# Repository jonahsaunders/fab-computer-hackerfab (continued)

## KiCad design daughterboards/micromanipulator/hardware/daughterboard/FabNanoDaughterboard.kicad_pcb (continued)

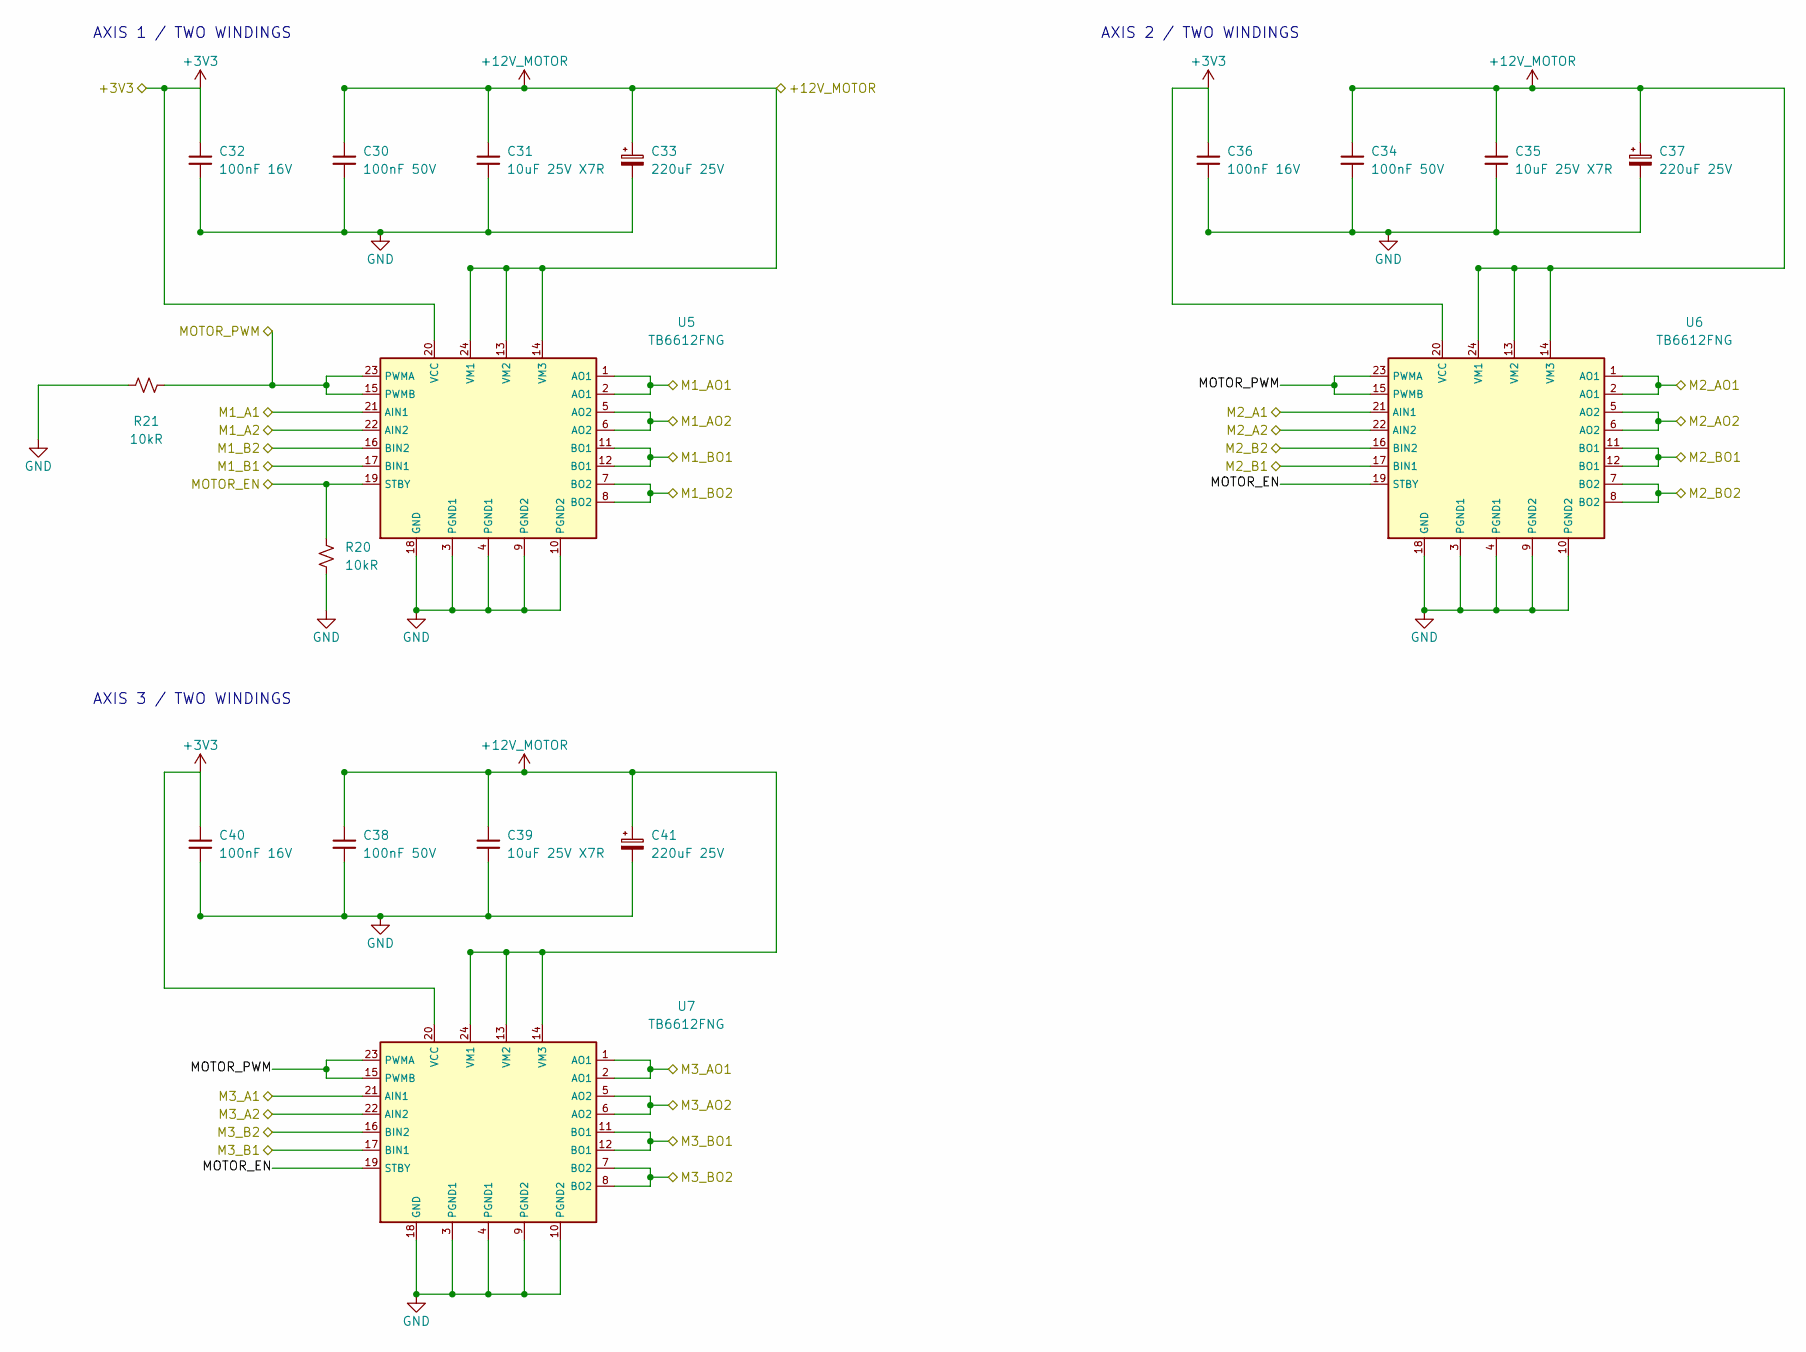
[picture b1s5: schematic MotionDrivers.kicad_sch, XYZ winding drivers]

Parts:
C30, C34, C38: 100nF 50V; C_0603_1608Metric; MPN CC0603KRX7R9BB104; LCSC C14663
C31, C35, C39: 10uF 25V X7R; C_0805_2012Metric; MPN C0805X7R106K250NT; LCSC C2835529
C32, C36, C40: 100nF 16V; C_0402_1005Metric; MPN CL05B104KO5NNNC; LCSC C1525
C33, C37, C41: 220uF 25V; CP_Elec_6.3x7.7; MPN 217EC0037; LCSC C42371908
R20, R21: 10kR; R_0603_1608Metric; MPN 0603WAF1002T5E; LCSC C25804
U5, U6, U7: TB6612FNG; SSOP-24_Toshiba_5.6x7.8mm_P0.65mm; MPN TB6612FNG(O,C,8,EL; LCSC C88224

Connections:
+3V3: C32.1, C36.1, C40.1, U5.20 (VCC), U6.20 (VCC), U7.20 (VCC); also elsewhere on the board
+12V_MOTOR: C30.1, C31.1, C33.1, C34.1, C35.1, C37.1, C38.1, C39.1, C41.1, U5.13 (VM2), U5.14 (VM3), U5.24 (VM1), U6.13 (VM2), U6.14 (VM3), U6.24 (VM1), U7.13 (VM2), U7.14 (VM3), U7.24 (VM1); also elsewhere on the board
/M1_A1: U5.21 (AIN1); also elsewhere on the board
/M1_A2: U5.22 (AIN2); also elsewhere on the board
/M1_AO1: U5.1 (AO1), U5.2 (AO1); also elsewhere on the board
/M1_AO2: U5.5 (AO2), U5.6 (AO2); also elsewhere on the board
/M1_B1: U5.17 (BIN1); also elsewhere on the board
/M1_B2: U5.16 (BIN2); also elsewhere on the board
/M1_BO1: U5.11 (BO1), U5.12 (BO1); also elsewhere on the board
/M1_BO2: U5.7 (BO2), U5.8 (BO2); also elsewhere on the board
/M2_A1: U6.21 (AIN1); also elsewhere on the board
/M2_A2: U6.22 (AIN2); also elsewhere on the board
/M2_AO1: U6.1 (AO1), U6.2 (AO1); also elsewhere on the board
/M2_AO2: U6.5 (AO2), U6.6 (AO2); also elsewhere on the board
/M2_B1: U6.17 (BIN1); also elsewhere on the board
/M2_B2: U6.16 (BIN2); also elsewhere on the board
/M2_BO1: U6.11 (BO1), U6.12 (BO1); also elsewhere on the board
/M2_BO2: U6.7 (BO2), U6.8 (BO2); also elsewhere on the board
/M3_A1: U7.21 (AIN1); also elsewhere on the board
/M3_A2: U7.22 (AIN2); also elsewhere on the board
/M3_AO1: U7.1 (AO1), U7.2 (AO1); also elsewhere on the board
/M3_AO2: U7.5 (AO2), U7.6 (AO2); also elsewhere on the board
/M3_B1: U7.17 (BIN1); also elsewhere on the board
/M3_B2: U7.16 (BIN2); also elsewhere on the board
/M3_BO1: U7.11 (BO1), U7.12 (BO1); also elsewhere on the board
/M3_BO2: U7.7 (BO2), U7.8 (BO2); also elsewhere on the board
/MOTOR_EN: R20.1, U5.19 (STBY), U6.19 (STBY), U7.19 (STBY); also elsewhere on the board
/MOTOR_PWM: R21.1, U5.15 (PWMB), U5.23 (PWMA), U6.15 (PWMB), U6.23 (PWMA), U7.15 (PWMB), U7.23 (PWMA); also elsewhere on the board
GND: C30.2, C31.2, C32.2, C33.2, C34.2, C35.2, C36.2, C37.2, C38.2, C39.2, C40.2, C41.2, R20.2, R21.2, U5.3 (PGND1), U5.4 (PGND1), U5.9 (PGND2), U5.10 (PGND2), U5.18 (GND), U6.3 (PGND1), U6.4 (PGND1), U6.9 (PGND2), U6.10 (PGND2), U6.18 (GND), U7.3 (PGND1), U7.4 (PGND1), U7.9 (PGND2), U7.10 (PGND2), U7.18 (GND); also elsewhere on the board

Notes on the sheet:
AXIS 1 / TWO WINDINGS
AXIS 2 / TWO WINDINGS
AXIS 3 / TWO WINDINGS

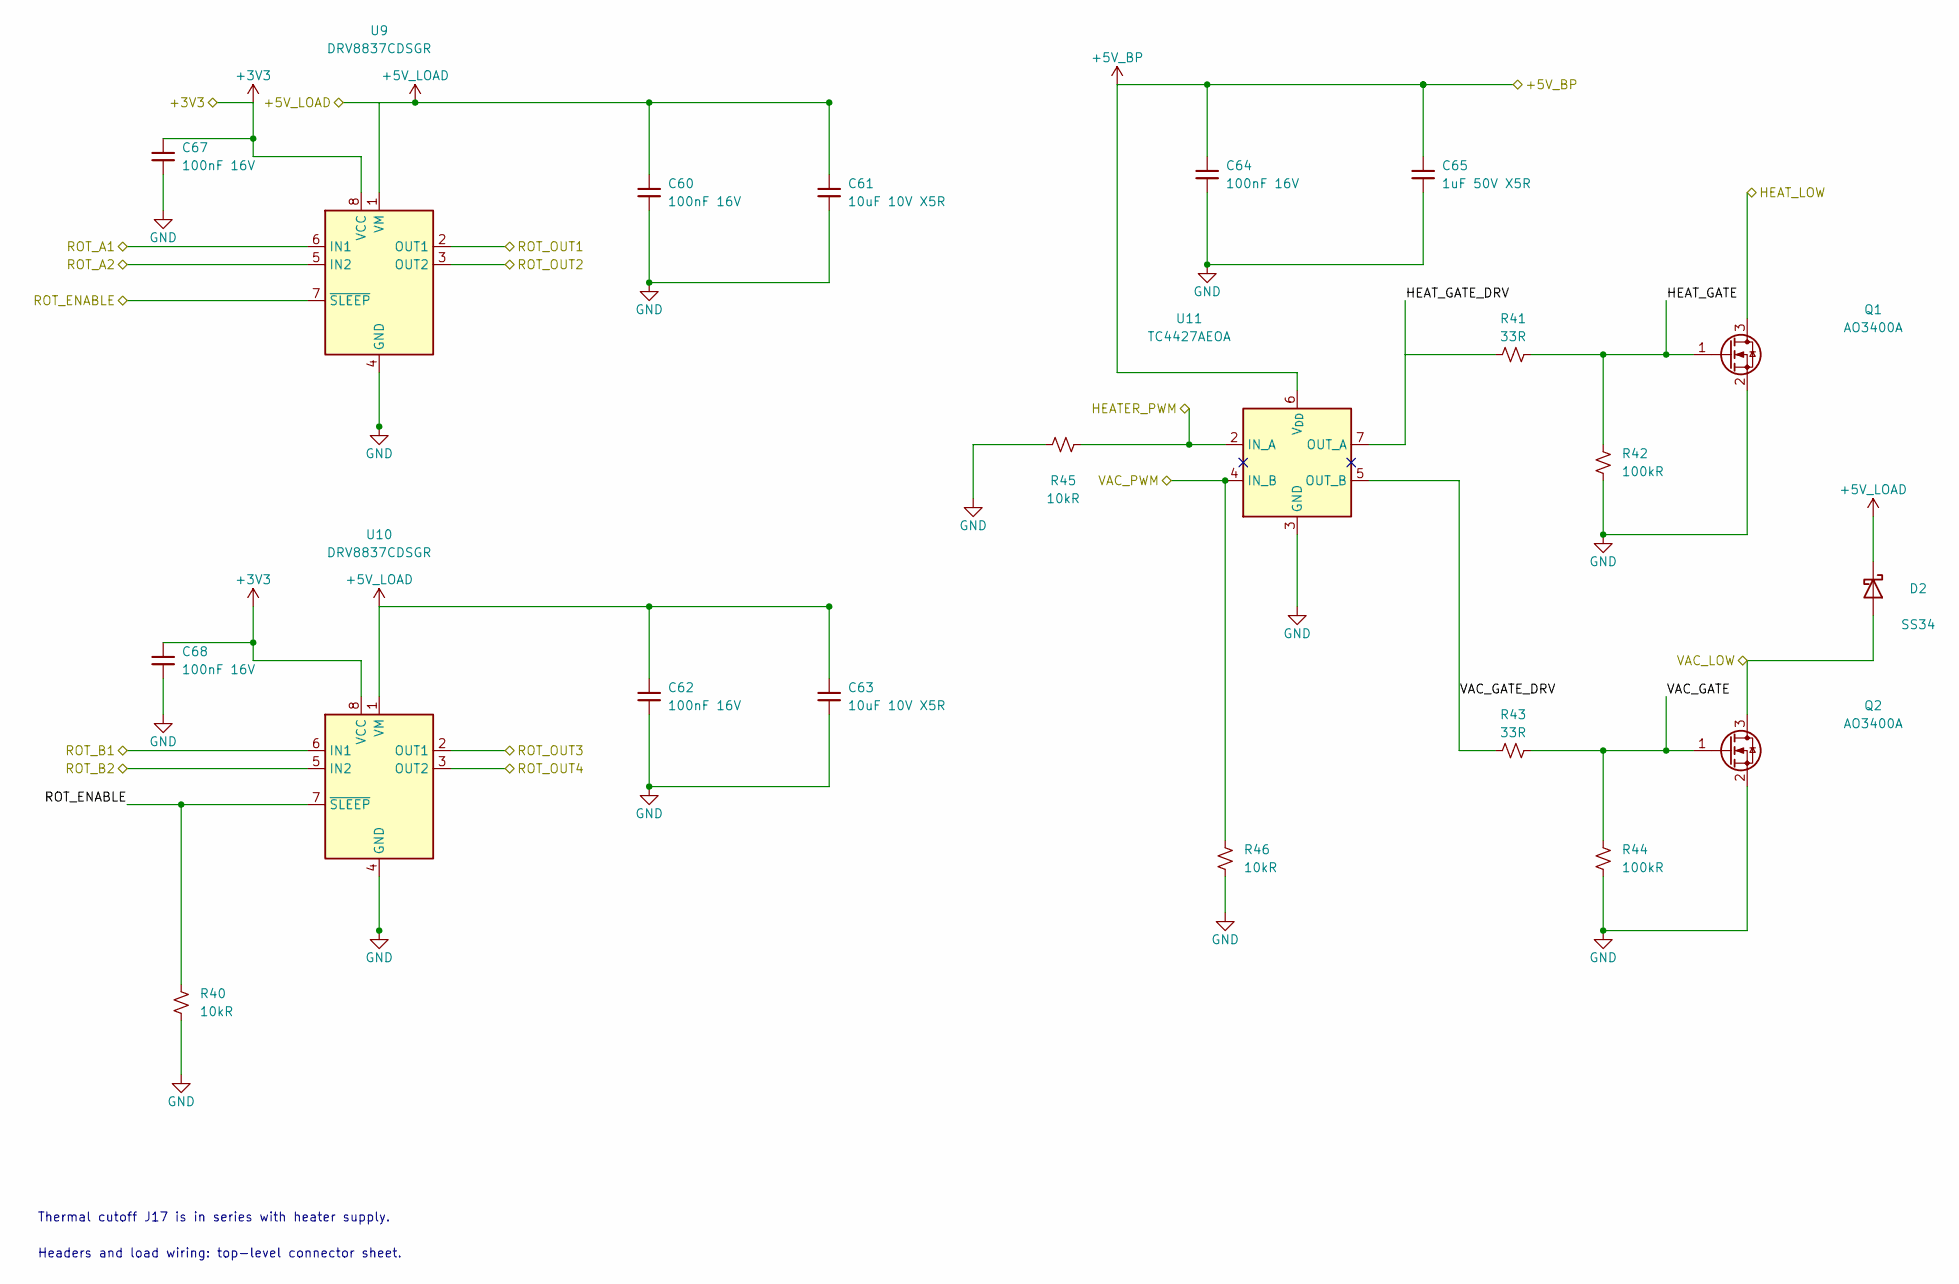
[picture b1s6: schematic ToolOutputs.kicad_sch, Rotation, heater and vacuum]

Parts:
C60, C62, C64, C67, C68: 100nF 16V; C_0402_1005Metric; MPN CL05B104KO5NNNC; LCSC C1525
C61, C63: 10uF 10V X5R; C_0603_1608Metric; MPN CL10A106KP8NNNC; LCSC C19702
C65: 1uF 50V X5R; C_0603_1608Metric; MPN CL10A105KB8NNNC; LCSC C15849
D2: SS34; D_SMA; MPN SS34; LCSC C8678
Q1, Q2: AO3400A; SOT-23; MPN AO3400A; LCSC C20917
R40, R45, R46: 10kR; R_0603_1608Metric; MPN 0603WAF1002T5E; LCSC C25804
R41, R43: 33R; R_0603_1608Metric; MPN 0603WAF330JT5E; LCSC C23140
R42, R44: 100kR; R_0603_1608Metric; MPN 0603WAF1003T5E; LCSC C25803
U9, U10: DRV8837CDSGR; Texas_DSG0008A_WSON-8-1EP_2x2mm_P0.5mm_EP0.9x1.6mm; MPN DRV8837CDSGR; LCSC C191000
U11: TC4427AEOA; SOIC-8_3.9x4.9mm_P1.27mm; MPN TC4427AEOA; LCSC C18690

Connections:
+3V3: C67.1, C68.1, U9.8 (VCC), U10.8 (VCC); also elsewhere on the board
+5V_BP: C64.1, C65.1, U11.6 (V_{DD}); also elsewhere on the board
+5V_LOAD: C60.1, C61.1, C62.1, C63.1, D2.1 (K), U9.1 (VM), U10.1 (VM); also elsewhere on the board
/HEATER_PWM: R45.1, U11.2 (IN_A); also elsewhere on the board
/HEAT_LOW: Q1.3 (D); also elsewhere on the board
/ROT_A1: U9.6 (IN1); also elsewhere on the board
/ROT_A2: U9.5 (IN2); also elsewhere on the board
/ROT_B1: U10.6 (IN1); also elsewhere on the board
/ROT_B2: U10.5 (IN2); also elsewhere on the board
/ROT_ENABLE: R40.1, U9.7 (~SLEEP), U10.7 (~SLEEP); also elsewhere on the board
/ROT_OUT1: U9.2 (OUT1); also elsewhere on the board
/ROT_OUT2: U9.3 (OUT2); also elsewhere on the board
/ROT_OUT3: U10.2 (OUT1); also elsewhere on the board
/ROT_OUT4: U10.3 (OUT2); also elsewhere on the board
/ToolOutputs/HEAT_GATE: Q1.1 (G), R41.2, R42.1
/ToolOutputs/HEAT_GATE_DRV: R41.1, U11.7 (OUT_A)
/ToolOutputs/VAC_GATE: Q2.1 (G), R43.2, R44.1
/ToolOutputs/VAC_GATE_DRV: R43.1, U11.5 (OUT_B)
/VAC_LOW: D2.2 (A), Q2.3 (D); also elsewhere on the board
/VAC_PWM: R46.1, U11.4 (IN_B); also elsewhere on the board
GND: C60.2, C61.2, C62.2, C63.2, C64.2, C65.2, C67.2, C68.2, Q1.2 (S), Q2.2 (S), R40.2, R42.2, R44.2, R45.2, R46.2, U9.4 (GND), U9.9 (GND), U10.4 (GND), U10.9 (GND), U11.3 (GND); also elsewhere on the board

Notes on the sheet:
Thermal cutoff J17 is in series with heater supply.
Headers and load wiring: top-level connector sheet.

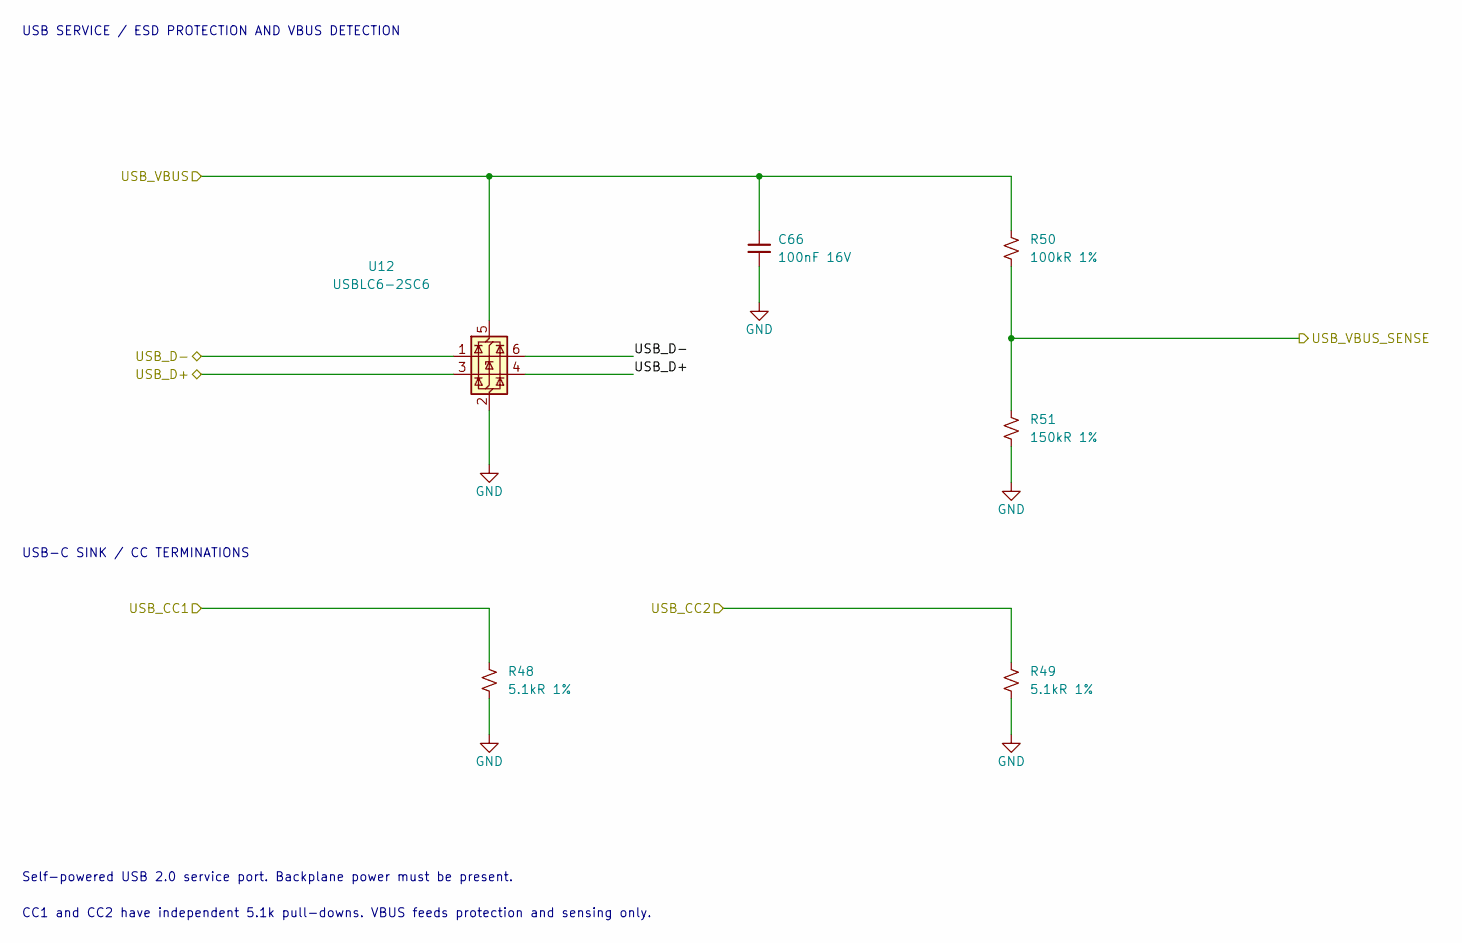
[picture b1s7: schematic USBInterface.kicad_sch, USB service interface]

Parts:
C66: 100nF 16V; C_0402_1005Metric; MPN CL05B104KO5NNNC; LCSC C1525
R48, R49: 5.1kR 1%; R_0603_1608Metric; MPN 0603WAF5101T5E; LCSC C23186
R50: 100kR 1%; R_0603_1608Metric; MPN 0603WAF1003T5E; LCSC C25803
R51: 150kR 1%; R_0603_1608Metric; MPN 0603WAF1503T5E; LCSC C22807
U12: USBLC6-2SC6; SOT-23-6; MPN USBLC6-2SC6; LCSC C7519

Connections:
/USB_CC1: R48.1; also elsewhere on the board
/USB_CC2: R49.1; also elsewhere on the board
/USB_D+: U12.3 (I/O2), U12.4 (I/O2); also elsewhere on the board
/USB_D-: U12.1 (I/O1), U12.6 (I/O1); also elsewhere on the board
/USB_VBUS: C66.1, R50.1, U12.5 (VBUS); also elsewhere on the board
/USB_VBUS_SENSE: R50.2, R51.1; also elsewhere on the board
GND: C66.2, R48.2, R49.2, R51.2, U12.2 (GND); also elsewhere on the board

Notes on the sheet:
USB SERVICE / ESD PROTECTION AND VBUS DETECTION
USB-C SINK / CC TERMINATIONS
Self-powered USB 2.0 service port. Backplane power must be present.
CC1 and CC2 have independent 5.1k pull-downs. VBUS feeds protection and sensing only.

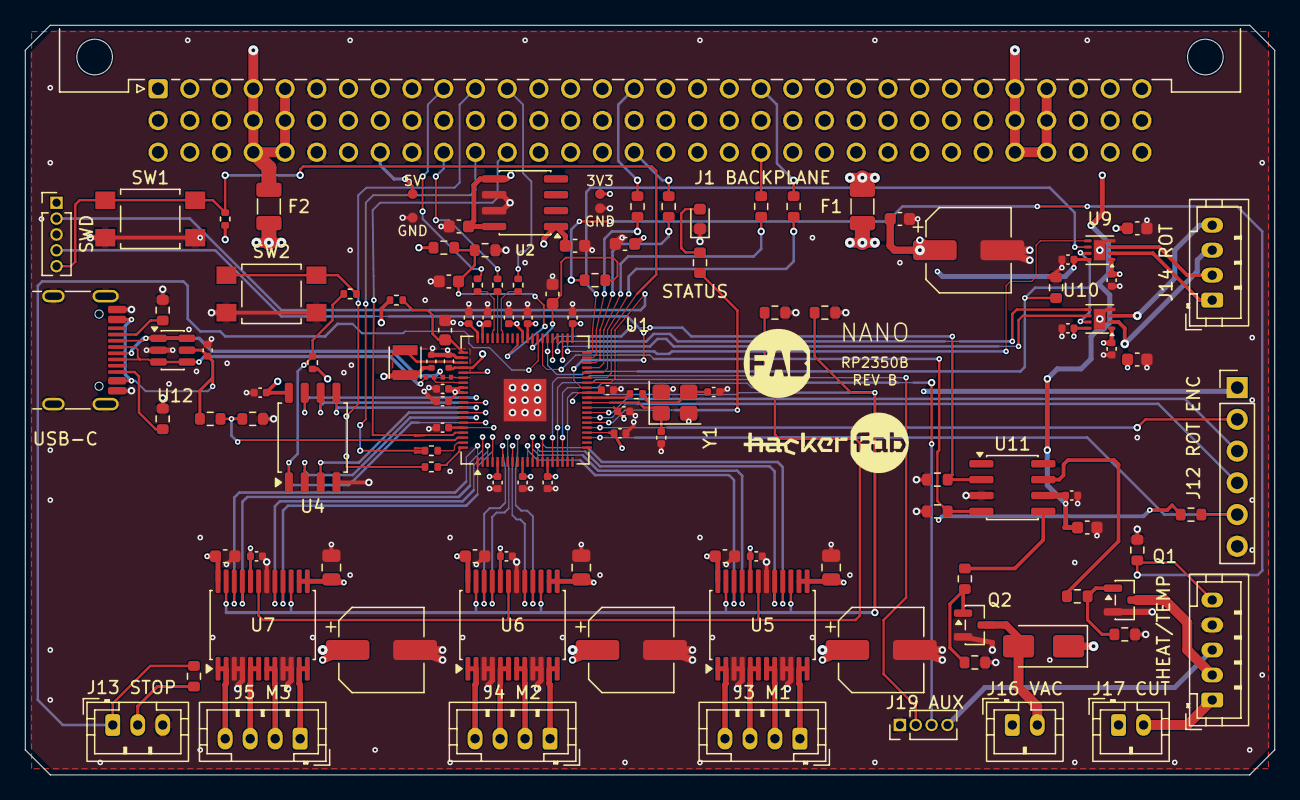
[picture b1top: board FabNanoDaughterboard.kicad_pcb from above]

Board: 4 copper layers, 100.0 x 60.0 mm, 121 parts (0 on the bottom side), 105 nets.

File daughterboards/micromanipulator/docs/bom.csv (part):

Reference,Value,Footprint,Manufacturer part number,Manufacturer,LCSC,Quantity,Procurement status
J1,DIN96 / male right-angle,FabNano:DIN96_Male_Horizontal,9001-11961C00A,WingTAT,C5173361,1,Manufacturer hole pattern and JLCPCB assembly catalog checked 2026-11-07; confirm order inventory
J2,SWD / RP2350,Connector_PinHeader_1.27mm:PinHeader_1x05_P1.27mm_Vertical,PH1.27-01-05PZD,XUNPU,C41360740,1,Manufacturer hole pattern and JLCPCB assembly catalog checked 2026-11-07; confirm order inventory
J3,MOTOR 1,Connector_JST:JST_PH_B4B-PH-K_1x04_P2.00mm_Vertical,B4B-PH-K-S(LF)(SN),JST,C131334,1,Manufacturer hole pattern and JLCPCB assembly catalog checked 2026-11-07; confirm order inventory
J4,MOTOR 2,Connector_JST:JST_PH_B4B-PH-K_1x04_P2.00mm_Vertical,B4B-PH-K-S(LF)(SN),JST,C131334,1,Manufacturer hole pattern and JLCPCB assembly catalog checked 2026-11-07; confirm order inventory
J5,MOTOR 3,Connector_JST:JST_PH_B4B-PH-K_1x04_P2.00mm_Vertical,B4B-PH-K-S(LF)(SN),JST,C131334,1,Manufacturer hole pattern and JLCPCB assembly catalog checked 2026-11-07; confirm order inventory
J12,ROTATION ENCODER,Connector_PinHeader_2.54mm:PinHeader_1x06_P2.54mm_Vertical,2.54-1x6PStraight pin,BOOMELE,C37208,1,Manufacturer hole pattern and JLCPCB assembly catalog checked 2026-11-07; confirm order inventory
J13,ENDSTOP,Connector_JST:JST_PH_B3B-PH-K_1x03_P2.00mm_Vertical,B3B-PH-K-S(LF)(SN),JST,C131339,1,Manufacturer hole pattern and JLCPCB assembly catalog checked 2026-11-07; confirm order inventory
J14,ROTATION MOTOR,Connector_JST:JST_PH_B4B-PH-K_1x04_P2.00mm_Vertical,B4B-PH-K-S(LF)(SN),JST,C131334,1,Manufacturer hole pattern and JLCPCB assembly catalog checked 2026-11-07; confirm order inventory
J15,HEATER + TEMP,Connector_JST:JST_PH_B5B-PH-K_1x05_P2.00mm_Vertical,B5B-PH-K-S(LF)(SN),JST,C157993,1,Manufacturer hole pattern and JLCPCB assembly catalog checked 2026-11-07; confirm order inventory
J16,VACUUM / 5 V,Connector_JST:JST_PH_B2B-PH-K_1x02_P2.00mm_Vertical,B2B-PH-K-S(LF)(SN),JST,C131337,1,Manufacturer hole pattern and JLCPCB assembly catalog checked 2026-11-07; confirm order inventory
J17,THERMAL CUTOFF,Connector_JST:JST_PH_B2B-PH-K_1x02_P2.00mm_Vertical,B2B-PH-K-S(LF)(SN),JST,C131337,1,Manufacturer hole pattern and JLCPCB assembly catalog checked 2026-11-07; confirm order inventory
J18,USB-C / SERVICE,Connector_USB:USB_C_Receptacle_HRO_TYPE-C-31-M-12,TYPE-C-31-M-12,HRO,C165948,1,"Exact part, package/model and JLCPCB catalog checked 2026-11-07; confirm inventory"
J19,TOOL PWM,Connector_PinHeader_1.27mm:PinHeader_1x04_P1.27mm_Vertical,PH1.27-01-04PZD,XUNPU,C41360739,1,Manufacturer hole pattern and JLCPCB assembly catalog checked 2026-11-07; confirm order inventory
C10,4.7uF 16V X5R,Capacitor_SMD:C_0603_1608Metric,CL10A475KO8NNNC,Samsung Electro-Mechanics,C19666,1,Samsung bias data and JLCPCB catalog/package checked 2026-11-07; confirm order inventory
C11,4.7uF 6.3V X5R,FabNano:C_0402_RP2350_Regulator,GRM155R60J475ME47D,Murata,C82453,1,Exact existing part and JLCPCB code checked 2026-11-07; confirm inventory
C12,4.7uF 6.3V X5R,FabNano:C_0402_RP2350_Regulator,GRM155R60J475ME47D,Murata,C82453,1,Exact existing part and JLCPCB code checked 2026-11-07; confirm inventory
C13,100nF 25V,Capacitor_SMD:C_0402_1005Metric,CL05B104KA5NNNC,Samsung Electro-Mechanics,C155422,1,Manufacturer dimensions/ratings and JLCPCB catalog checked 2026-11-07; confirm order inventory
C14,15pF C0G,Capacitor_SMD:C_0402_1005Metric,0402CG150J500NT,Guangdong Fenghua Advanced Technology,C1548,1,Manufacturer dimensions/ratings and JLCPCB catalog checked 2026-11-07; confirm order inventory
C15,15pF C0G,Capacitor_SMD:C_0402_1005Metric,0402CG150J500NT,Guangdong Fenghua Advanced Technology,C1548,1,Manufacturer dimensions/ratings and JLCPCB catalog checked 2026-11-07; confirm order inventory
C16,100nF 25V,Capacitor_SMD:C_0402_1005Metric,CL05B104KA5NNNC,Samsung Electro-Mechanics,C155422,1,Manufacturer dimensions/ratings and JLCPCB catalog checked 2026-11-07; confirm order inventory
C17,100nF 25V,Capacitor_SMD:C_0402_1005Metric,CL05B104KA5NNNC,Samsung Electro-Mechanics,C155422,1,Manufacturer dimensions/ratings and JLCPCB catalog checked 2026-11-07; confirm order inventory
C18,100nF 25V,Capacitor_SMD:C_0402_1005Metric,CL05B104KA5NNNC,Samsung Electro-Mechanics,C155422,1,Manufacturer dimensions/ratings and JLCPCB catalog checked 2026-11-07; confirm order inventory
C19,100nF 25V,Capacitor_SMD:C_0402_1005Metric,CL05B104KA5NNNC,Samsung Electro-Mechanics,C155422,1,Manufacturer dimensions/ratings and JLCPCB catalog checked 2026-11-07; confirm order inventory
C20,100nF 25V,Capacitor_SMD:C_0402_1005Metric,CL05B104KA5NNNC,Samsung Electro-Mechanics,C155422,1,Manufacturer dimensions/ratings and JLCPCB catalog checked 2026-11-07; confirm order inventory
C21,100nF 25V,Capacitor_SMD:C_0402_1005Metric,CL05B104KA5NNNC,Samsung Electro-Mechanics,C155422,1,Manufacturer dimensions/ratings and JLCPCB catalog checked 2026-11-07; confirm order inventory
C22,100nF 25V,Capacitor_SMD:C_0402_1005Metric,CL05B104KA5NNNC,Samsung Electro-Mechanics,C155422,1,Manufacturer dimensions/ratings and JLCPCB catalog checked 2026-11-07; confirm order inventory
C23,100nF 25V,Capacitor_SMD:C_0402_1005Metric,CL05B104KA5NNNC,Samsung Electro-Mechanics,C155422,1,Manufacturer dimensions/ratings and JLCPCB catalog checked 2026-11-07; confirm order inventory
C24,100nF 25V,Capacitor_SMD:C_0402_1005Metric,CL05B104KA5NNNC,Samsung Electro-Mechanics,C155422,1,Manufacturer dimensions/ratings and JLCPCB catalog checked 2026-11-07; confirm order inventory
C25,100nF 25V,Capacitor_SMD:C_0402_1005Metric,CL05B104KA5NNNC,Samsung Electro-Mechanics,C155422,1,Manufacturer dimensions/ratings and JLCPCB catalog checked 2026-11-07; confirm order inventory
C26,100nF 25V,Capacitor_SMD:C_0402_1005Metric,CL05B104KA5NNNC,Samsung Electro-Mechanics,C155422,1,Manufacturer dimensions/ratings and JLCPCB catalog checked 2026-11-07; confirm order inventory
C27,100nF 25V,Capacitor_SMD:C_0402_1005Metric,CL05B104KA5NNNC,Samsung Electro-Mechanics,C155422,1,Manufacturer dimensions/ratings and JLCPCB catalog checked 2026-11-07; confirm order inventory
C53,100nF 25V,Capacitor_SMD:C_0402_1005Metric,CL05B104KA5NNNC,Samsung Electro-Mechanics,C155422,1,Manufacturer dimensions/ratings and JLCPCB catalog checked 2026-11-07; confirm order inventory
C54,100nF 25V,Capacitor_SMD:C_0402_1005Metric,CL05B104KA5NNNC,Samsung Electro-Mechanics,C155422,1,Manufacturer dimensions/ratings and JLCPCB catalog checked 2026-11-07; confirm order inventory
L2,3.3uH,Hack_Passives:L_Murata_DFE252012F_2.5x2.0mm,DFE252012F-3R3M=P2,Murata,C2041573,1,Manufacturer dimensions/ratings and JLCPCB catalog checked 2026-11-07; confirm order inventory
R7,27R,FabNano:R_0201_Yageo_Reflow,RC0201FR-0727RL,YAGEO,C273268,1,JLCPCB Standard assembly catalog and manufacturer land pattern checked 2026-11-07; confirm order inventory
R8,27R,FabNano:R_0201_Yageo_Reflow,RC0201FR-0727RL,YAGEO,C273268,1,JLCPCB Standard assembly catalog and manufacturer land pattern checked 2026-11-07; confirm order inventory
R10,33R,Resistor_SMD:R_0402_1005Metric,0402WGF330JTCE,Uniroyal Electronics,C25105,1,Manufacturer dimensions/ratings and JLCPCB catalog checked 2026-11-07; confirm order inventory
R11,10kR,Resistor_SMD:R_0402_1005Metric,0402WGF1002TCE,Uniroyal Electronics,C25744,1,Manufacturer dimensions/ratings and JLCPCB catalog checked 2026-11-07; confirm order inventory
R12,1kR,Resistor_SMD:R_0402_1005Metric,0402WGF1001TCE,Uniroyal Electronics,C11702,1,Manufacturer dimensions/ratings and JLCPCB catalog checked 2026-11-07; confirm order inventory
R13,10kR,Resistor_SMD:R_0402_1005Metric,0402WGF1002TCE,Uniroyal Electronics,C25744,1,Manufacturer dimensions/ratings and JLCPCB catalog checked 2026-11-07; confirm order inventory
R14,1kR,Resistor_SMD:R_0402_1005Metric,0402WGF1001TCE,Uniroyal Electronics,C11702,1,Manufacturer dimensions/ratings and JLCPCB catalog checked 2026-11-07; confirm order inventory
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
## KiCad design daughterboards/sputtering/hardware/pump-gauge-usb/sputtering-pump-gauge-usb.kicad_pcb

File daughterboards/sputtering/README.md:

# Sputtering cards

Two cards for the sputtering backplane. No MCU on either; the backplane's RP2350B drives them.

[Repository overview](../../README.md#sputtering-cards) · [Review and validation](docs/validation.md) · [Manufacturing guide](../../docs/manufacturing/README.md#sputtering-cards)

| Board | Slot | Size | Open in KiCad 10 | Review |
| --- | --- | --- | --- | --- |
| Pump + gauge + USB | J1 | 100 × 65 mm, 2 layers | [Project](hardware/pump-gauge-usb/sputtering-pump-gauge-usb.kicad_pro) | [Schematic](docs/sputtering-pump-gauge-usb-schematic.pdf), [3D](docs/sputtering-pump-gauge-usb-3d.png), [BOM](../../docs/manufacturing/sputtering-pump-gauge-usb/BOM.csv) |
| Alicat | J2 | 100 × 85 mm, 2 layers | [Project](hardware/alicat/sputtering-alicat.kicad_pro) | [Schematic](docs/sputtering-alicat-schematic.pdf), [3D](docs/sputtering-alicat-3d.png), [BOM](../../docs/manufacturing/sputtering-alicat/BOM.csv) |

Keep this folder together: libraries resolve from [`hardware/libraries/`](hardware/libraries/).

The projects also use the standard symbol and footprint libraries installed with KiCad 10. Design sources, local libraries, schematic PDFs, renders and review notes live in this section. Fabrication exports follow the repository's shared manufacturing layout:

| Board | Fabrication | Assembly |
| --- | --- | --- |
| Pump + gauge + USB | [Gerbers and drills](../../docs/manufacturing/sputtering-pump-gauge-usb/Gerbers.zip) | [BOM](../../docs/manufacturing/sputtering-pump-gauge-usb/BOM.csv) · [CPL](../../docs/manufacturing/sputtering-pump-gauge-usb/CPL.csv) |
| Alicat | [Gerbers and drills](../../docs/manufacturing/sputtering-alicat/Gerbers.zip) | [BOM](../../docs/manufacturing/sputtering-alicat/BOM.csv) · [CPL](../../docs/manufacturing/sputtering-alicat/CPL.csv) |

## Backplane connections

Slot names below refer to the host: use **J1 for pump + gauge + USB** and **J2 for Alicat**. Both cards name their own DIN96 plug J1. These slot assignments use the host's slot-specific UART and AUX connections; the cards are not interchangeable between slots.

| Card | Backplane use |
| --- | --- |
| Pump + gauge + USB | UART0 pump (RS-485), GPIO40 direction; I²C0 gauge ADC (0x48); GPIO22/23 PIO-USB host |
| Alicat | UART1 argon, GPIO24/25 PIO UART oxygen (RS-232) |

## Review status

The [PR #16 connector update](https://github.com/jonahsaunders/fab-computer-hackerfab/pull/16), submitted by [jacobro100](https://github.com/jacobro100), adds pump-card screw terminals and male Alicat DB9 connectors. KiCad 10.0.6 reported no ERC errors or warnings and no DRC errors, unconnected items or schematic-parity findings. DRC reported **9 warnings on pump + gauge + USB** and **24 warnings on Alicat**. See the [review record](docs/validation.md) for categories, reproduction commands and remaining manufacturing and bench checks.

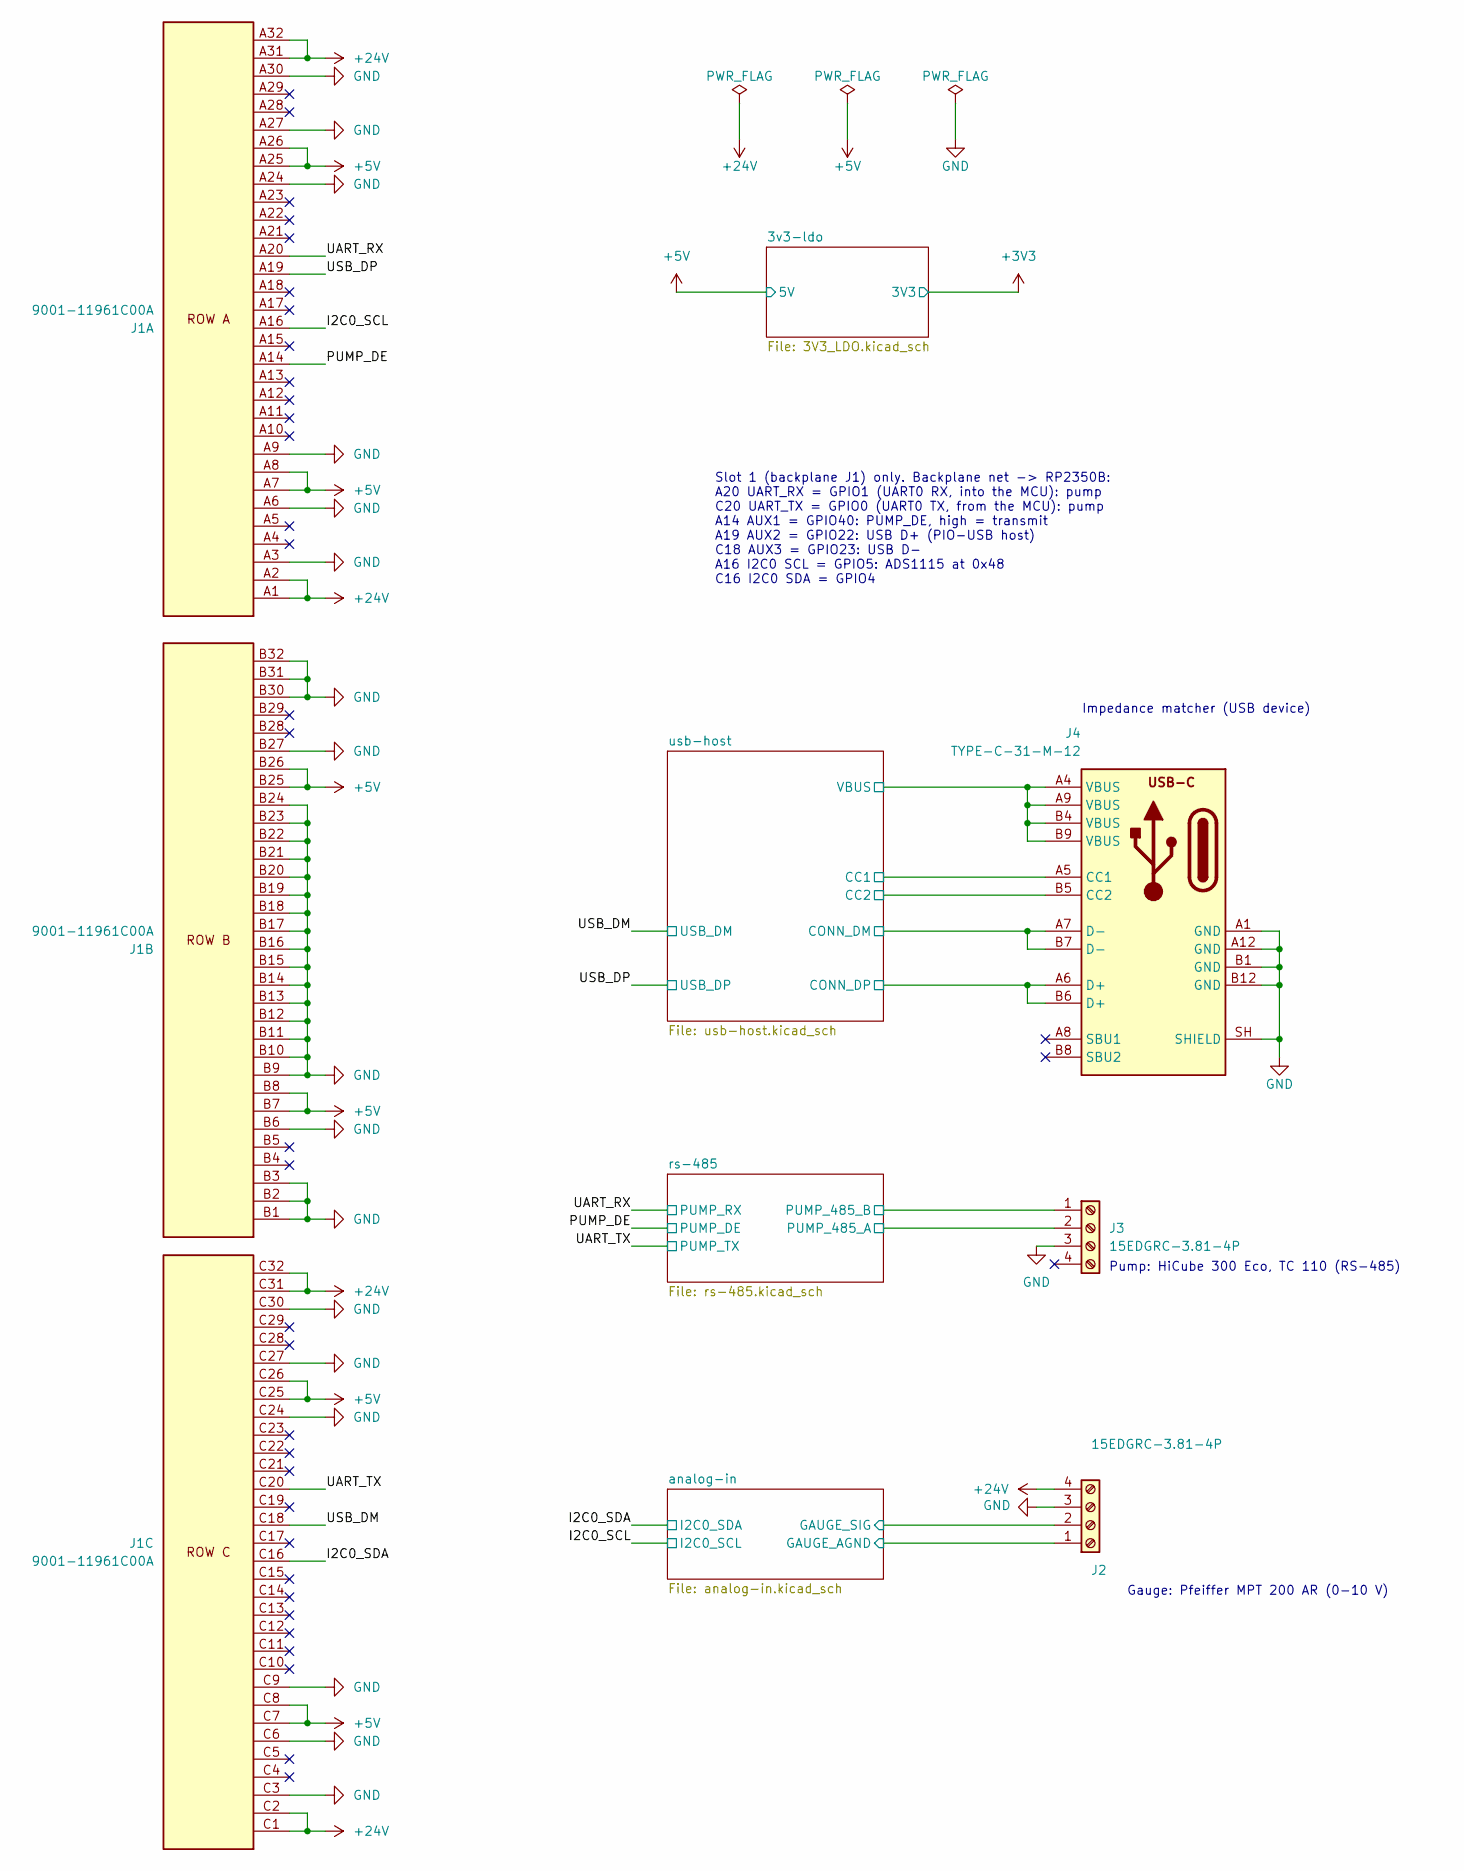
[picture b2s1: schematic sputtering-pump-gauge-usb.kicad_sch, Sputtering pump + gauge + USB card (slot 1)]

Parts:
J1: 9001-11961C00A; WingTAT_9001-11961C00A_DIN41612_C_3x32_RightAngle; LCSC C5173361
J2, J3: 15EDGRC-3.81-4P; Kangnex_WJ15EDGRC-3.81_1x04_P3.81mm_Horizontal; MPN Kangnex WJ15EDGRC-3.81-04P-14-00A; LCSC C7245
J4: TYPE-C-31-M-12; USB_C_Receptacle_HRO_TYPE-C-31-M-12; MPN TYPE-C-31-M-12; LCSC C165948

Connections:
+5V: J1.A7, J1.A8, J1.A25, J1.A26, J1.B7, J1.B8, J1.B25, J1.B26, J1.C7, J1.C8, J1.C25, J1.C26; also elsewhere on the board
+24V: J1.A1, J1.A2, J1.A31, J1.A32, J1.C1, J1.C2, J1.C31, J1.C32, J2.4
/I2C0_SCL: J1.A16; also elsewhere on the board
/I2C0_SDA: J1.C16; also elsewhere on the board
/PUMP_DE: J1.A14; also elsewhere on the board
/UART_RX: J1.A20; also elsewhere on the board
/UART_TX: J1.C20; also elsewhere on the board
/USB_DM: J1.C18; also elsewhere on the board
/USB_DP: J1.A19; also elsewhere on the board
/analog-in/GAUGE_AGND: J2.1; also elsewhere on the board
/analog-in/GAUGE_SIG: J2.2; also elsewhere on the board
/rs-485/PUMP_485_A: J3.2; also elsewhere on the board
/rs-485/PUMP_485_B: J3.1; also elsewhere on the board
/usb-host/CC1: J4.A5 (CC1); also elsewhere on the board
/usb-host/CC2: J4.B5 (CC2); also elsewhere on the board
/usb-host/CONN_DM: J4.A7 (D-), J4.B7 (D-); also elsewhere on the board
/usb-host/CONN_DP: J4.A6 (D+), J4.B6 (D+); also elsewhere on the board
/usb-host/VBUS: J4.A4 (VBUS), J4.A9 (VBUS), J4.B4 (VBUS), J4.B9 (VBUS); also elsewhere on the board
GND: J1.A3, J1.A6, J1.A9, J1.A24, J1.A27, J1.A30, J1.B1, J1.B2, J1.B3, J1.B6, J1.B9, J1.B10, J1.B11, J1.B12, J1.B13, J1.B14, J1.B15, J1.B16, J1.B17, J1.B18, J1.B19, J1.B20, J1.B21, J1.B22, J1.B23, J1.B24, J1.B27, J1.B30, J1.B31, J1.B32, J1.C3, J1.C6, J1.C9, J1.C24, J1.C27, J1.C30, J2.3, J3.3, J4.A1 (GND), J4.A12 (GND), J4.B1 (GND), J4.B12 (GND), J4.SH (SHIELD); also elsewhere on the board

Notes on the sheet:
Pump: HiCube 300 Eco, TC 110 (RS-485)
Impedance matcher (USB device)
Gauge: Pfeiffer MPT 200 AR (0-10 V)
Slot 1 (backplane J1) only. Backplane net -> RP2350B: A20 UART_RX = GPIO1 (UART0 RX, into the MCU): pump C20 UART_TX = GPIO0 (UART0 TX, from the MCU): pump A14 AUX1 = GPIO40: PUMP_DE, high = transmit A19 AUX2 = GPIO22: USB D+ (PIO-USB host) C18 AUX3 = GPIO23: USB D- A16 I2C0 SCL = GPIO5: ADS1115 at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

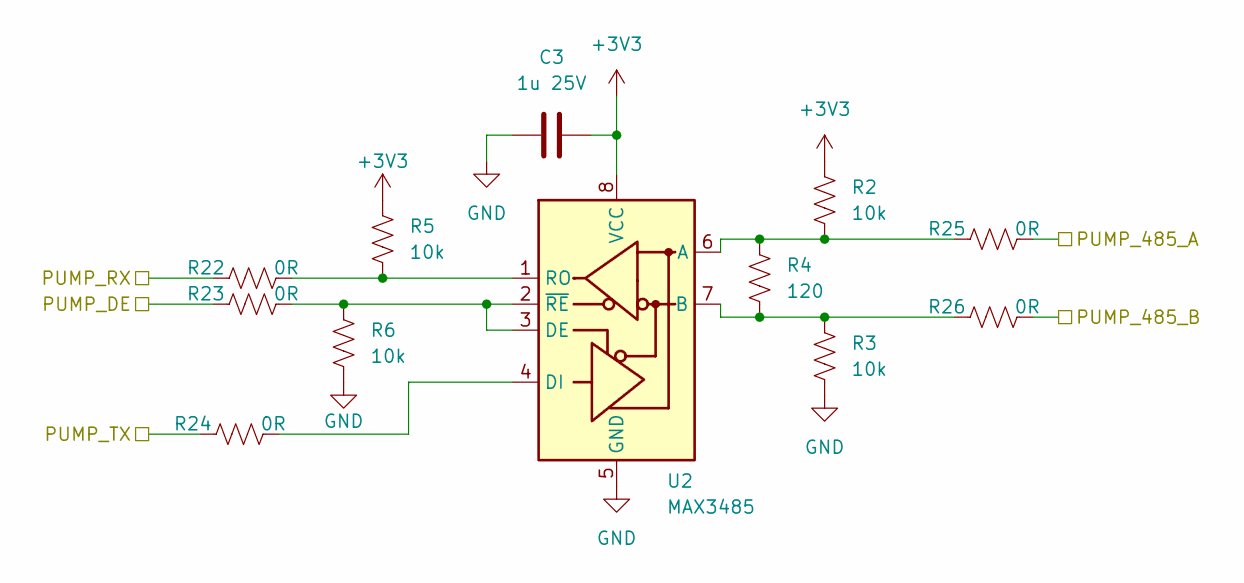
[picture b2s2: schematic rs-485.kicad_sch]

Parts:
C3: 1u 25V; C_0603_1608Metric; LCSC C15849
R2, R3, R5, R6: 10k; R_0603_1608Metric; LCSC C25804
R4: 120; R_0603_1608Metric; MPN UNI-ROYAL 0603WAF1200T5E; LCSC C22787
R22, R23, R24, R25, R26: 0R; R_0603_1608Metric; LCSC C21189
U2: MAX3485; SOIC-8_3.9x4.9mm_P1.27mm; MPN Maxim MAX3485ESA+T; LCSC C18148

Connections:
+3V3: C3.2, R2.1, R5.1, U2.8 (VCC); also elsewhere on the board
/PUMP_DE: R23.1; also elsewhere on the board
/UART_RX: R22.1; also elsewhere on the board
/UART_TX: R24.1; also elsewhere on the board
/rs-485/PUMP_485_A: R25.2; also elsewhere on the board
/rs-485/PUMP_485_B: R26.2; also elsewhere on the board
GND: C3.1, R3.2, R6.2, U2.5 (GND); also elsewhere on the board
unnamed: R2.2, R4.1, R25.1, U2.6 (A)
unnamed: R3.1, R4.2, R26.1, U2.7 (B)
unnamed: R6.1, R23.2, U2.2 (~RE), U2.3 (DE)
unnamed: R24.2, U2.4 (DI)
unnamed: R5.2, R22.2, U2.1 (RO)

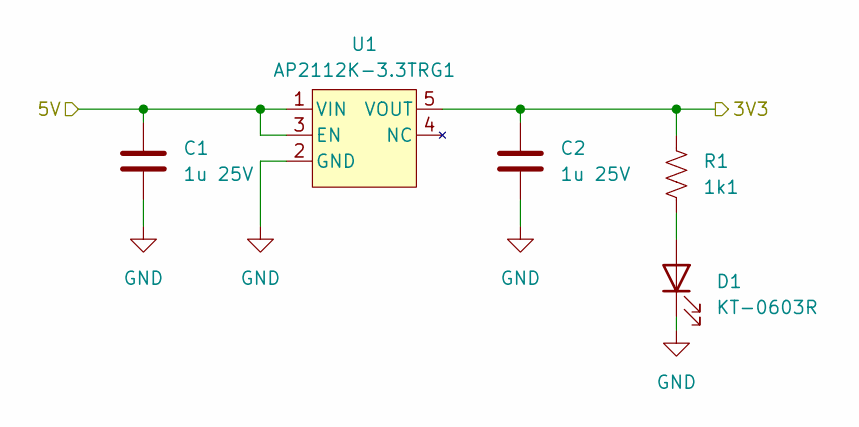
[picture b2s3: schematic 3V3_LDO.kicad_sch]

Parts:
C1, C2: 1u 25V; C_0603_1608Metric; LCSC C15849
D1: KT-0603R; LED_0603_1608Metric; MPN KT-0603R; LCSC C2286
R1: 1k1; R_0603_1608Metric; LCSC C22764
U1: AP2112K-3.3TRG1; SOT-23-5; LCSC C51118

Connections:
+3V3: C2.1, R1.1, U1.5 (VOUT); also elsewhere on the board
+5V: C1.1, U1.1 (VIN), U1.3 (EN); also elsewhere on the board
GND: C1.2, C2.2, D1.1 (K), U1.2 (GND); also elsewhere on the board
unnamed: D1.2 (A), R1.2
